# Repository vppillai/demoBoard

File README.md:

# demoBoard
This is a work in progres. Unless notified otherwise, donot assume sanity of the contents of this repo

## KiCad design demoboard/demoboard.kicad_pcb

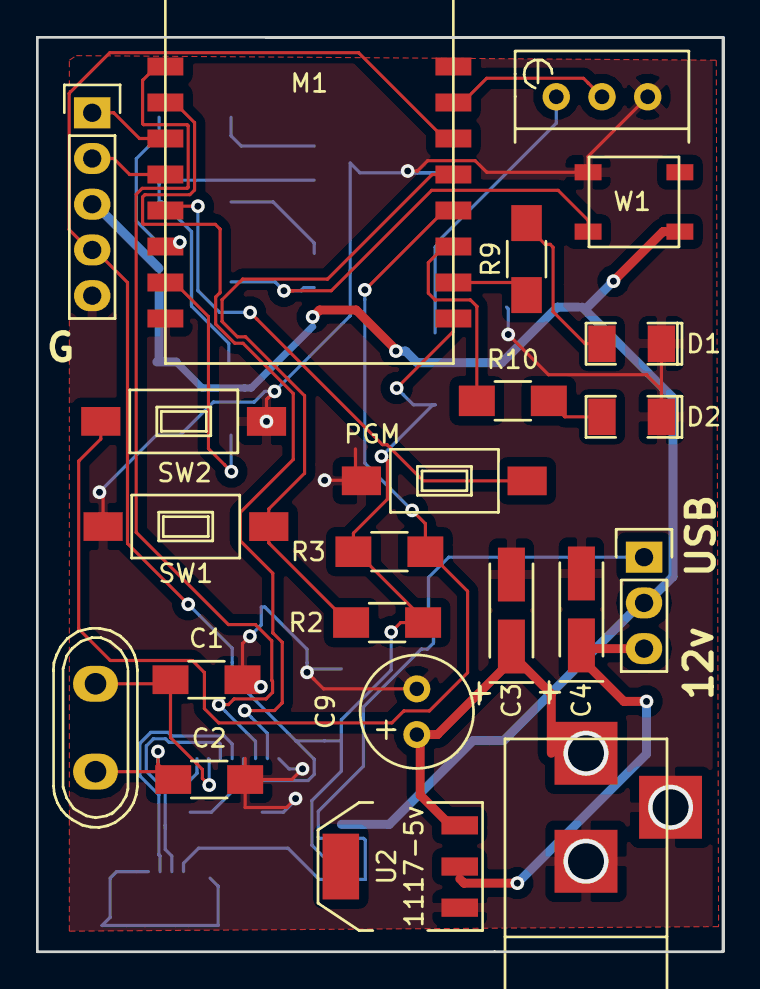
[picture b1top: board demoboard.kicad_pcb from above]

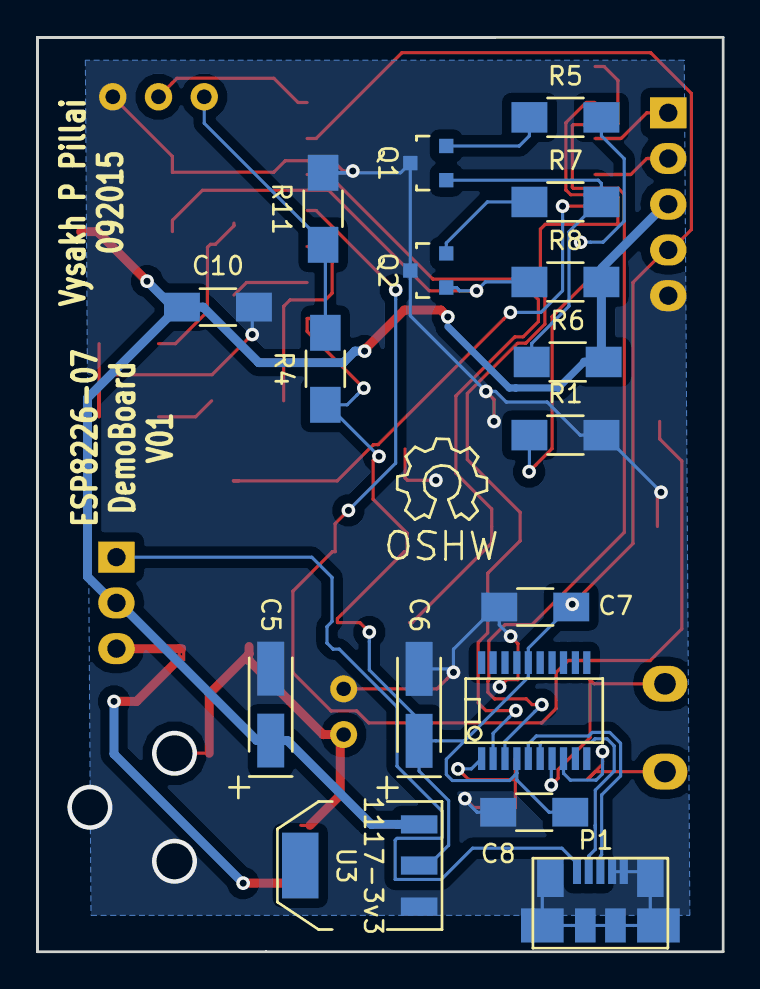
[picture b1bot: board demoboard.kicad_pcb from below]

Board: 2 copper layers, 38.1 x 50.8 mm, 39 parts (17 on the bottom side), 29 nets.

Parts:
C1, C2: 22pf; C_1206_HandSoldering
C3, C4, C5, C6: 10uf; TantalC_SizeA_EIA-3216_HandSoldering
C7, C8, C10: 0.1uf; C_1206_HandSoldering
C9: 1mf; Elko_vert_11.2x6.3mm_RM2.5_CopperClear
CON1: BARREL_JACK
D1: GREEN; SMD-1206_Pol
D2: RED; SMD-1206_Pol
JP1: JUMPER3; Pin_Header_Straight_1x03
M1: ESP-07
P1: USB_OTG; molex-microUSB
P2: header1; Pin_Header_Straight_1x05
PGM: PGM; SW_SPST_FSMSM
Q1, Q2: BC547; SOT-23
R1, R2, R3: 10K; R_1206_HandSoldering
R4: 220R; R_1206_HandSoldering
R5, R6, R7: 1K; R_1206_HandSoldering
R8: 1.5K; R_1206_HandSoldering
R9, R10: 120E; R_1206_HandSoldering
R11: 100R; R_1206_HandSoldering
RV1: 10K; Potentiometer_Bourns_3296W_3-8Zoll_Inline_ScrewUp
SW1, SW2: UI1; SW_SPST_FSMSM
U1: CH340G; SSOP-20
U2: 1117-5v; SOT-223
U3: 1117-3v3; SOT-223
W1: ws2812b; ws2812B
Y1: 12MHz; Crystal_HC50-U_Vertical

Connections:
3v3: C6.1, C7.1, C8.1, M1.9, M1.14, P2.4, R2.2, R3.2, R4.1, U1.4, U1.16, U3.2
3v3In: M1.6, R5.2
5v: C5.1, C10.1, JP1.2, P2.3, R6.2, R8.2, U3.3, W1.1
5vOut: Q2.1, R8.1, W1.4
12v: C3.1, C9.1, CON1.1, U2.3
GND: C1.2, C2.2, C3.2, C4.2, C5.2, C6.2, C7.2, C8.2, C9.2, C10.2, CON1.2, CON1.3, D1.1, D2.1, M1.8, P1.4, P1.5, P1.6, P2.5, PGM.1, Q1.3, Q2.3, R1.2, R11.2, RV1.3, SW1.2, SW2.2, U1.1, U2.1, U3.1, W1.3
JP1.1: M1.3, P2.1
JP1.2: M1.4, P2.2
unnamed: C1.1, U1.7, Y1.1
unnamed: C2.1, U1.8, Y1.2
unnamed: D1.2, R9.2
unnamed: D2.2, R10.2
unnamed: M1.5, PGM.2
unnamed: M1.7, R1.1
unnamed: M1.10, R9.1
unnamed: M1.11, R10.1
unnamed: M1.12, R3.1, SW2.1
unnamed: M1.13, R2.1, SW1.1
unnamed: M1.15, RV1.2
unnamed: Q1.1, R6.1, R7.2
unnamed: Q1.2, R5.1
unnamed: Q2.2, R7.1
unnamed: R4.2, R11.1, RV1.1
RX: M1.1, U1.3
TX: M1.2, U1.2
UD+: P1.3, U1.5
UD-: P1.2, U1.6
VLDO5v: C4.1, JP1.3, U2.2
VUSB: JP1.1, P1.1

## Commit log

2015-08-18 rev0.1-1
2015-08-18 adding modules dir
2015-08-19 added ESP
2015-08-19 cleared module dummy
2015-08-29 layoutv1
2015-09-01 usb and esp 3d models
2015-09-01 ufl connector added to 3d model
2015-09-02 via cleanup, trace width and barrelplug vias
2015-09-03 lot f correction in routing and corrected solder mask clearence
2015-09-03 removed cap libs
2015-09-03 strengthened power lines. shortned traces
2015-09-03 oshpark order
2015-09-03 3d images added
